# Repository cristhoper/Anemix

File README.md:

Codigo para comunicacion entre Arduino y Qt para proyecto Anemix de LuxiaLighting

[Anemix de Luxia](http://www.luxialighting.com/aporta.php/es/productos/ver-producto-unico/theanemix-home-collection/)

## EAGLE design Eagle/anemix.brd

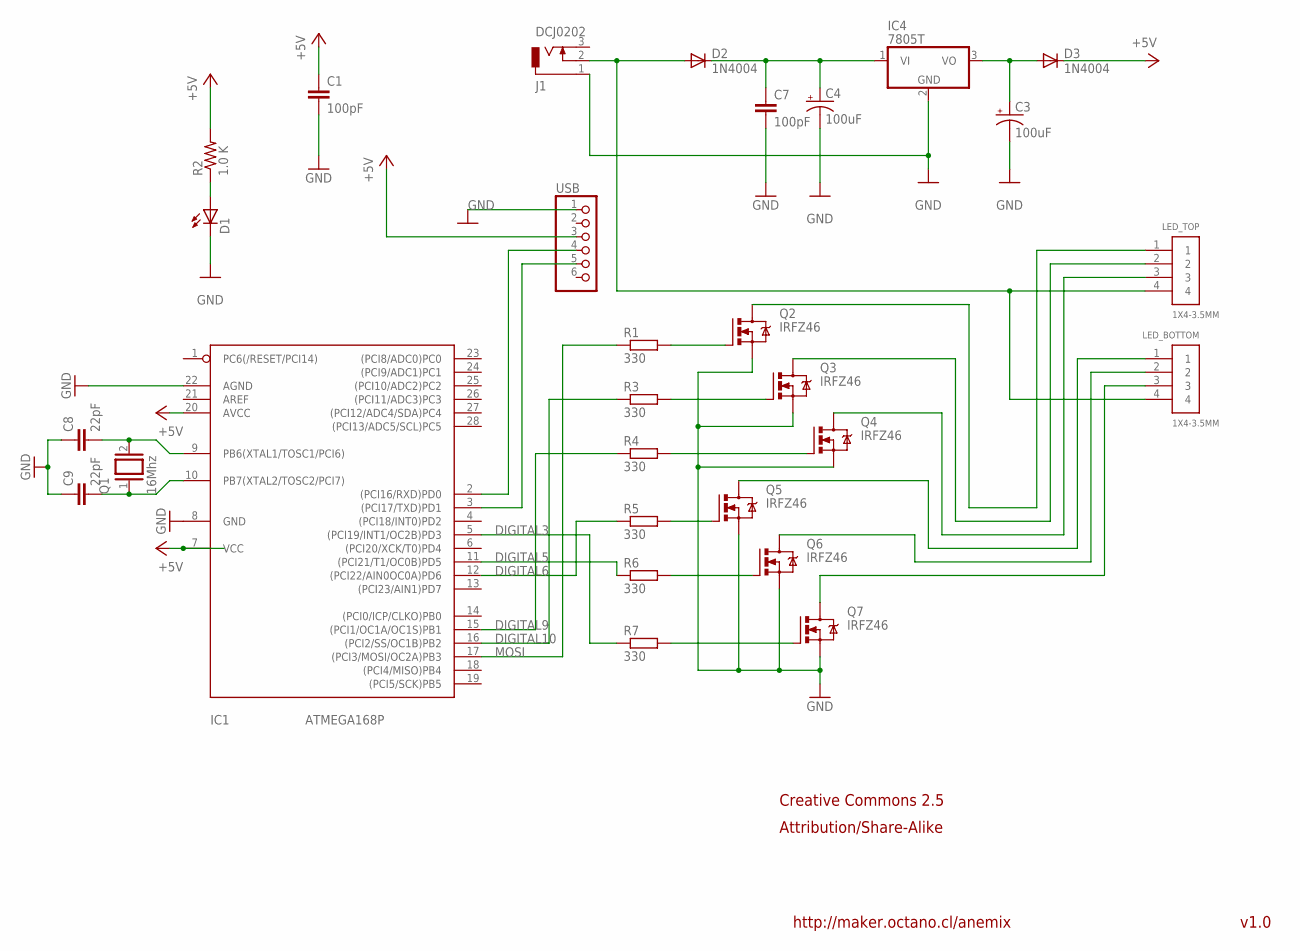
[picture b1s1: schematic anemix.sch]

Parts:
C1, C7: 100pF; C025-025X050
C3, C4: 100uF; E2,5-7
C8, C9: 22pF; C025-025X050
D1: LED3MM
D2, D3: 1N4004; DO41-10
IC1: ATMEGA168P; DIL28/3
IC4: 7805T; TO220H
J1: DCJ0202
LED_BOTTOM: 1X4-3.5MM; 1X04-3.5MM
LED_TOP: 1X4-3.5MM; 1X04-3.5MM
Q1: 16Mhz; QS
Q2, Q3, Q4, Q5, Q6, Q7: IRFZ46; TO220BH
R1, R3, R4, R5, R6, R7: 330; 0207/10
R2: 1.0 K; 0204/7
USB: PINHD-1X6; 1X06

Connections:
+5V: C1.1, D3.C, IC1.7 (VCC), IC1.20 (AVCC), R2.2, USB.3
DIGITAL3: IC1.5 ((PCI19/INT1/OC2B)PD3), R7.1
DIGITAL5: IC1.11 ((PCI21/T1/OC0B)PD5), R6.1
DIGITAL6: IC1.12 ((PCI22/AIN0OC0A)PD6), R5.1
DIGITAL9: IC1.15 ((PCI1/OC1A/OC1S)PB1), R4.1
DIGITAL10: IC1.16 ((PCI2/SS/OC1B)PB2), R3.1
GND: C1.2, C3.-, C4.-, C7.2, C8.1, C9.1, D1.K (C), IC1.8 (GND), IC1.22 (AGND), IC4.2 (GND), J1.1, Q2.S, Q3.S, Q4.S, Q5.S, Q6.S, Q7.S, USB.1
MOSI: IC1.17 ((PCI3/MOSI/OC2A)PB3), R1.1
unnamed: C8.2, IC1.9 (PB6(XTAL1/TOSC1/PCI6)), Q1.2
unnamed: C9.2, IC1.10 (PB7(XTAL2/TOSC2/PCI7)), Q1.1
unnamed: D1.A, R2.1
unnamed: IC1.3 ((PCI17/TXD)PD1), USB.5
unnamed: C4.+, C7.1, D2.C, IC4.1 (VI)
unnamed: Q2.G, R1.2
unnamed: Q3.G, R3.2
unnamed: Q4.G, R4.2
unnamed: IC1.2 ((PCI16/RXD)PD0), USB.4
unnamed: Q5.G, R5.2
unnamed: LED_BOTTOM.1, Q5.D
unnamed: LED_BOTTOM.2, Q6.D
unnamed: LED_BOTTOM.3, Q7.D
unnamed: Q6.G, R6.2
unnamed: Q7.G, R7.2
unnamed: D2.A, J1.2, LED_BOTTOM.4, LED_TOP.4
unnamed: C3.+, D3.A, IC4.3 (VO)
unnamed: LED_TOP.1, Q2.D
unnamed: LED_TOP.2, Q3.D
unnamed: LED_TOP.3, Q4.D

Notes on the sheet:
v1.0
http://maker.octano.cl/anemix
Creative Commons 2.5
Attribution/Share-Alike

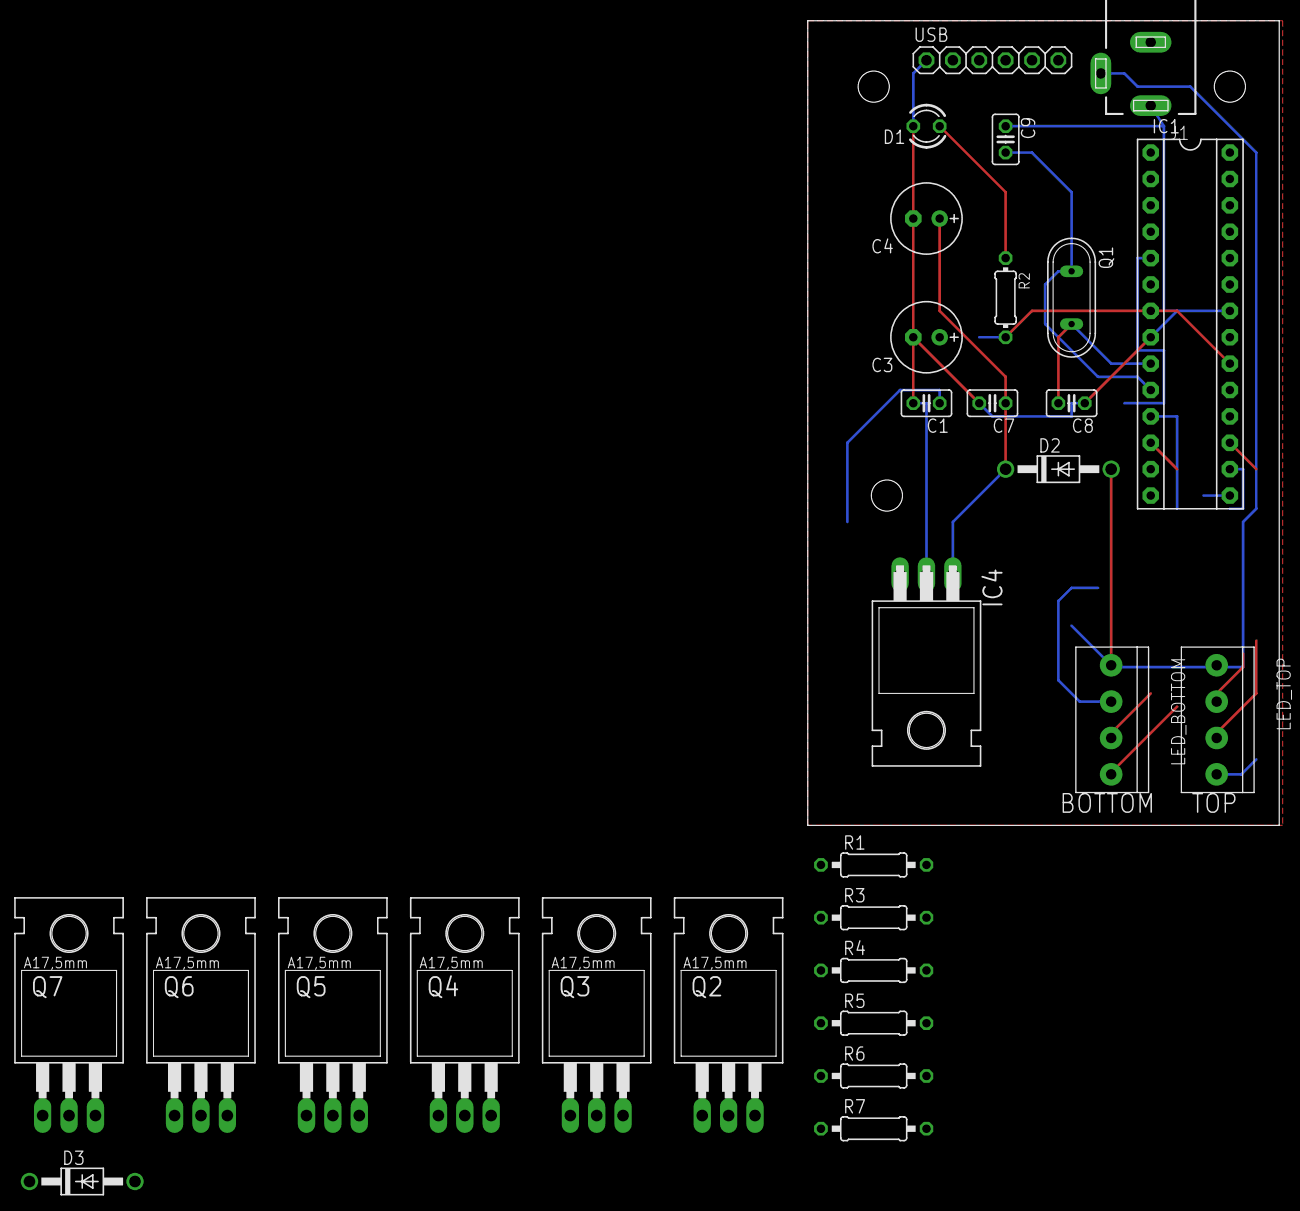
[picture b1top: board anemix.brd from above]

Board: 2 copper layers, 45.4 x 77.5 mm, 29 parts (0 on the bottom side), 28 nets.

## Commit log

2014-01-24 POPULATE
2014-01-24 DEL: debug & repeated symbols
2014-01-24 ADD: README.md
